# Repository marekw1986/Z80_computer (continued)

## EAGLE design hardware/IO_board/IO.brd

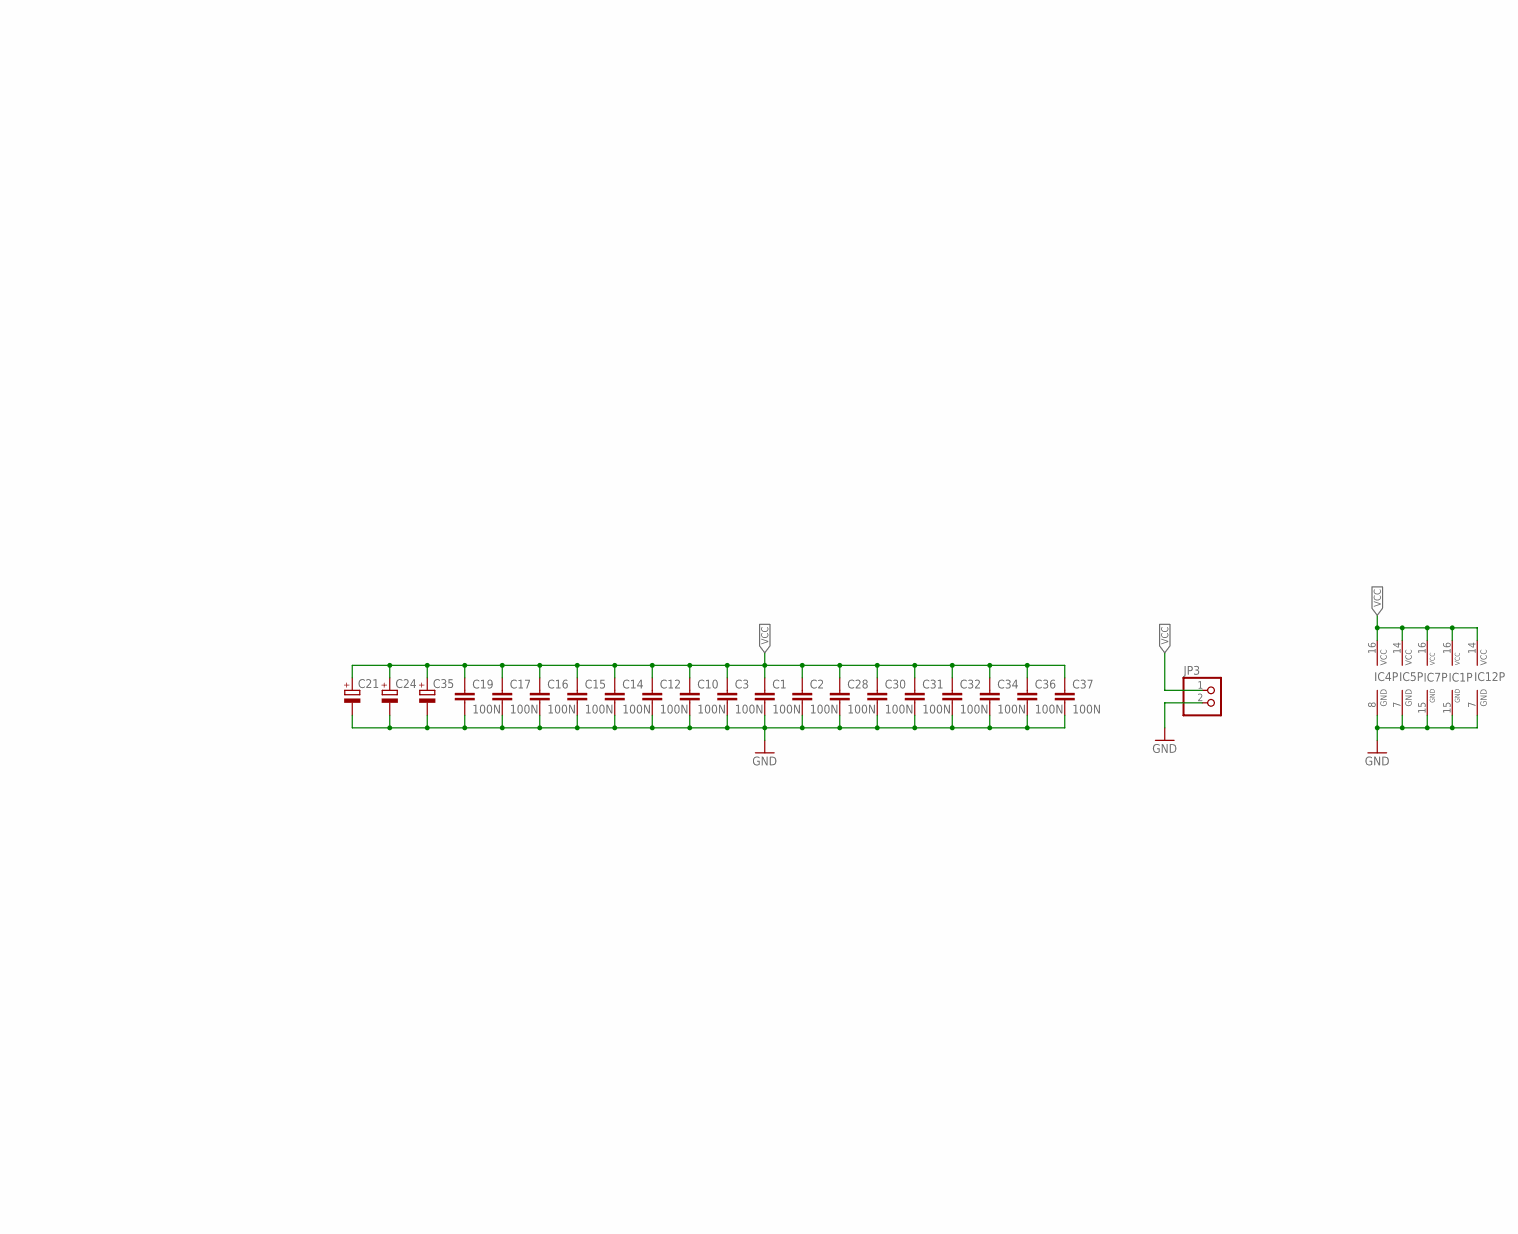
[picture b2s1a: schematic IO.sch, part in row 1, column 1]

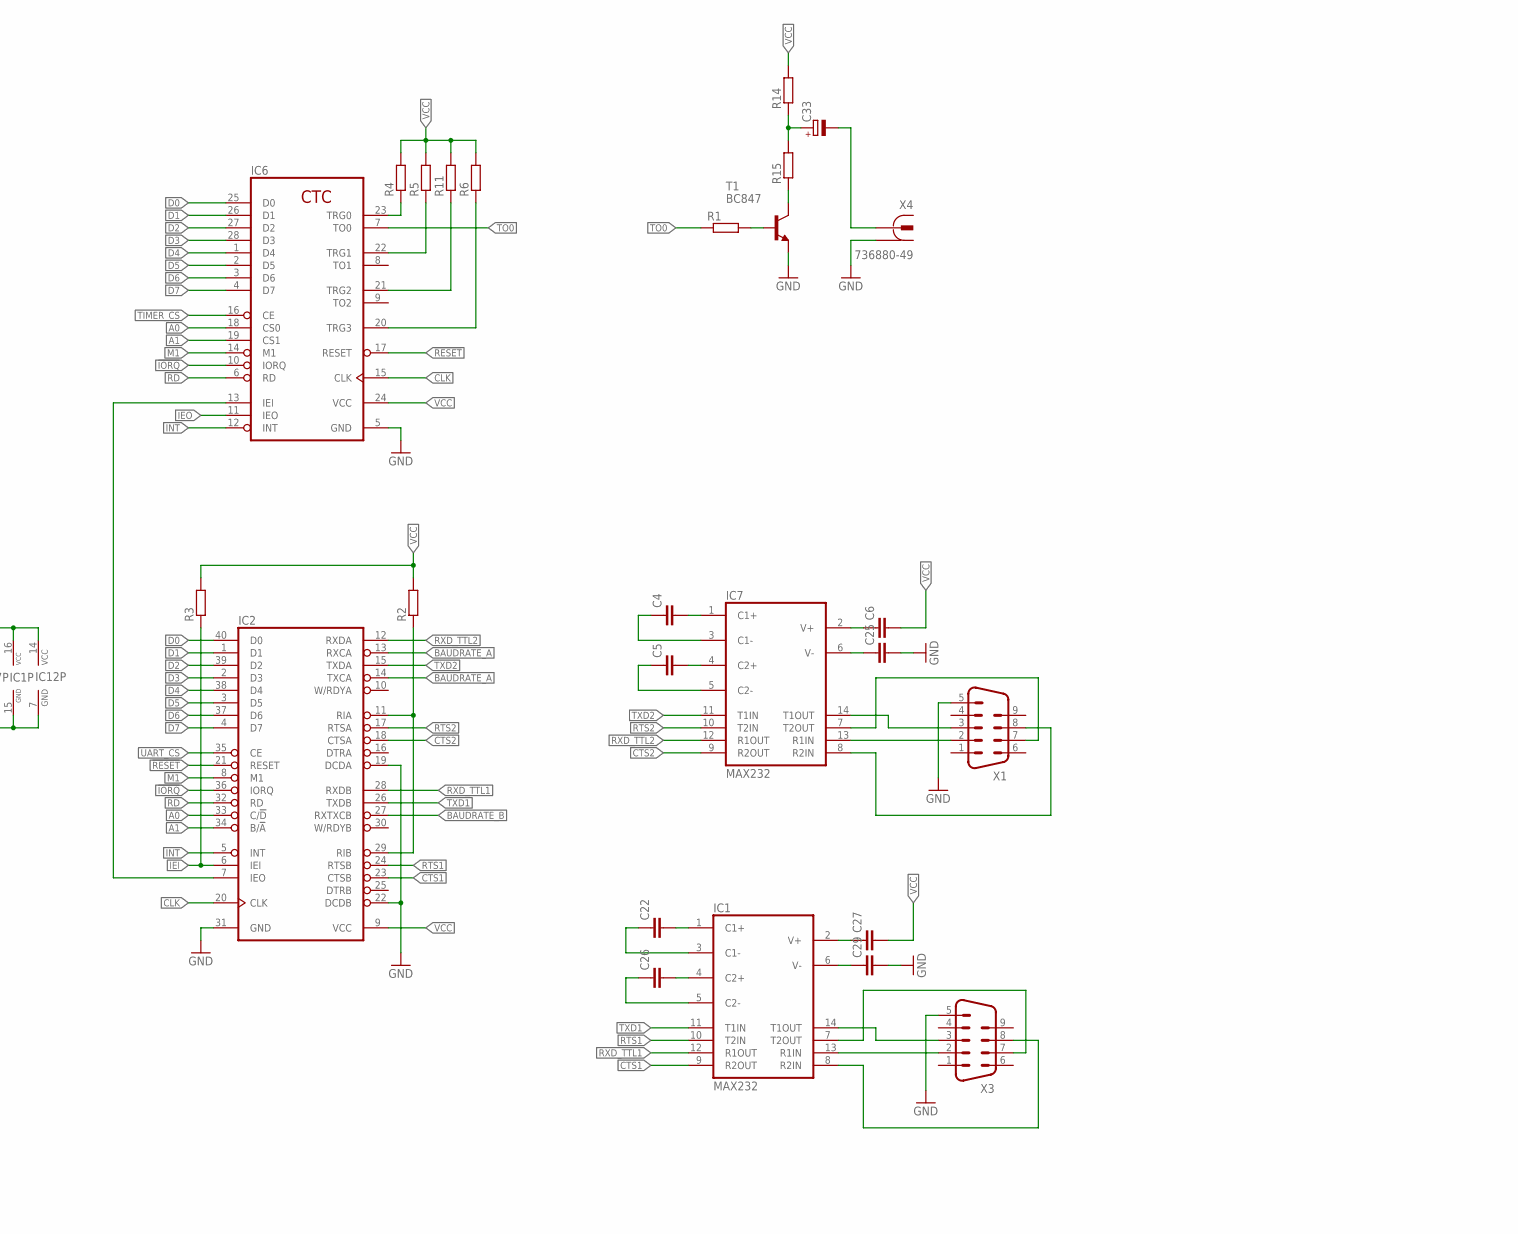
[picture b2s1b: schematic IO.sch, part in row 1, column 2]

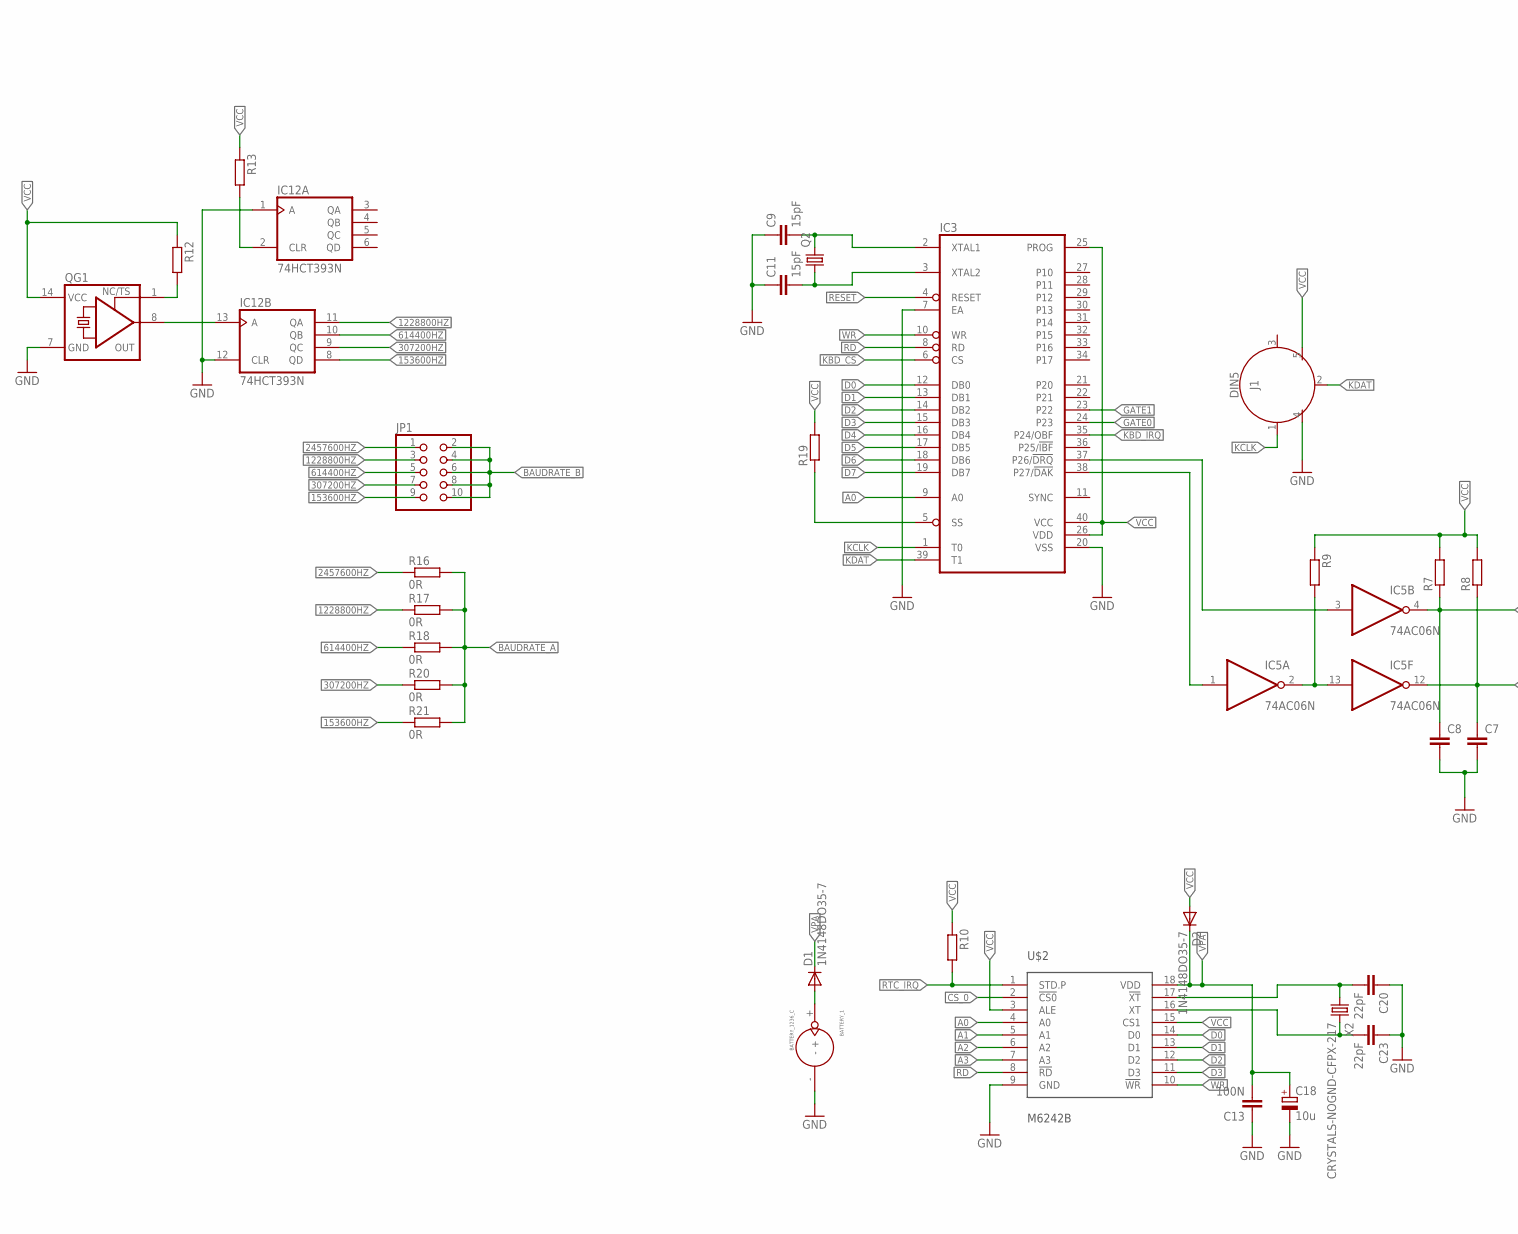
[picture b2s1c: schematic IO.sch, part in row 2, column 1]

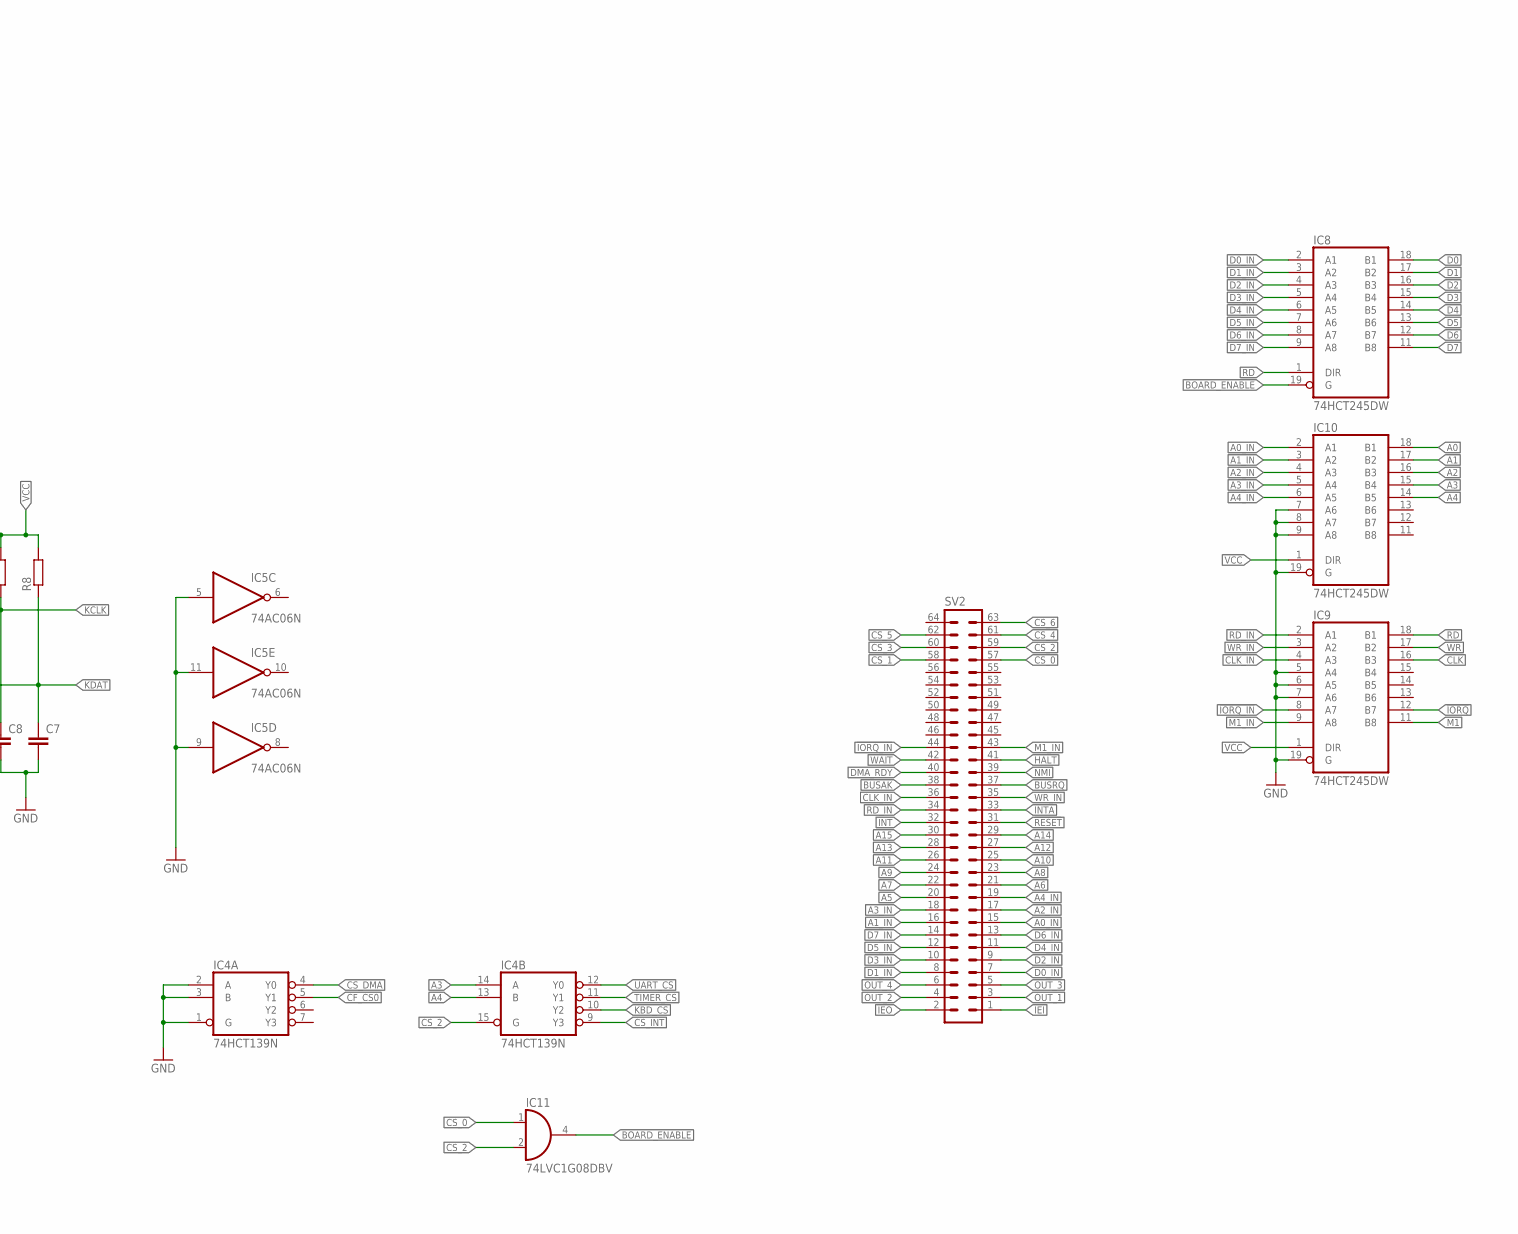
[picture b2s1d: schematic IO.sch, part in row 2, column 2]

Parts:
BATTERY_1: BATTERY_1236_C
C1, C3, C10, C12, C13, C14, C15, C16, C17, C19, C28, C30, C31, C32, C34, C36, C37: 100N; C0603
C2: 100N; C1206
C4, C5, C6, C7, C8, C22, C25, C26, C27, C29: C-EUC0603; C0603
C9, C11: 15pF; C0603
C18: 10u; SMC_B
C20, C23: 22pF; C0603
C21, C24: CPOL-EUSMCB; SMC_B
C33: CPOL-EUE2-4; E2-4
C35: CPOL-EUE5-10.5; E5-10,5
D1, D2: 1N4148DO35-7; DO35-7
IC1, IC7: MAX232; DIL16
IC2: Z80DART; DIL40
IC3: UPI-8042AH; DIL40
IC4: 74HCT139N; DIL16
IC5: 74AC06N; DIL14
IC6: Z80CTC; DIL28
IC8, IC9, IC10: 74HCT245DW; SO20W
IC11: 74LVC1G08DBV; SOT23-5
IC12: 74HCT393N; DIL14
J1: DIN5; DIN5-RA-PTH
JP1: PINHD-2X5; 2X05
JP3: PINHD-1X2/90; 1X02/90
Q2: CRYSTALHC49S; HC49/S
QG1: XO-14; DIL14S
R1, R2, R4, R5, R9, R10, R11, R12, R13, R15: R-EU_R0603; R0603
R3, R6, R19: R-EU_0204/5; 0204/5
R7, R14: R-EU_0204/7; 0204/7
R8: R-EU_M0805; M0805
R16, R17, R18, R20, R21: 0R; R0603
SV2: ML64L
T1: BC847; SOT23
U$2: M6242B; DIL18
X1, X3: M09HP
X2: CRYSTALS-NOGND-CFPX-217; 3.2X1.5-2-PAD
X4: 736880-49

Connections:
153600HZ: IC12.8 (QD), JP1.9, R21.1
307200HZ: IC12.9 (QC), JP1.7, R20.1
614400HZ: IC12.10 (QB), JP1.5, R18.1
1228800HZ: IC12.11 (QA), JP1.3, R17.1
2457600HZ: IC12.13 (A), JP1.1, QG1.8 (OUT), R16.1
!IORQ: IC2.36 (IORQ), IC6.10 (IORQ), IC9.12 (B7)
!IORQ_IN: IC9.8 (A7), SV2.44
!RESET: IC2.21 (RESET), IC3.4 (RESET), IC6.17 (RESET), SV2.31
A0: IC2.33 (C/!D), IC3.9 (A0), IC6.18 (CS0), IC10.18 (B1), U$2.4 (A0)
A0_IN: IC10.2 (A1), SV2.15
A1: IC2.34 (B/!A), IC6.19 (CS1), IC10.17 (B2), U$2.5 (A1)
A1_IN: IC10.3 (A2), SV2.16
A2: IC10.16 (B3), U$2.6 (A2)
A2_IN: IC10.4 (A3), SV2.17
A3: IC4.14 (A), IC10.15 (B4), U$2.7 (A3)
A3_IN: IC10.5 (A4), SV2.18
A4: IC4.13 (B), IC10.14 (B5)
A4_IN: IC10.6 (A5), SV2.19
A5: SV2.20
A6: SV2.21
A7: SV2.22
A8: SV2.23
A9: SV2.24
A10: SV2.25
A11: SV2.26
A12: SV2.27
A13: SV2.28
A14: SV2.29
A15: SV2.30
BAUDRATE_A: IC2.13 (RXCA), IC2.14 (TXCA), R16.2, R17.2, R18.2, R20.2, R21.2
BAUDRATE_B: IC2.27 (RXTXCB), JP1.2, JP1.4, JP1.6, JP1.8, JP1.10
BOARD_ENABLE: IC8.19 (G), IC11.4 (O)
BUSAK: SV2.38
BUSRQ: SV2.37
CF_CS0: IC4.5 (Y1)
CLK: IC2.20 (CLK), IC6.15 (CLK), IC9.16 (B3)
CLK_IN: IC9.4 (A3), SV2.36
CS_0: IC11.1 (I0), SV2.57, U$2.2 (!CS0)
CS_1: SV2.58
CS_2: IC4.15 (G), IC11.2 (I1), SV2.59
CS_3: SV2.60
CS_4: SV2.61
CS_5: SV2.62
CS_6: SV2.63
CS_DMA: IC4.4 (Y0)
CS_INT: IC4.9 (Y3)
CTS1: IC1.9 (R2OUT), IC2.23 (CTSB)
CTS1_IN: IC1.8 (R2IN), X3.8
CTS2: IC2.18 (CTSA), IC7.9 (R2OUT)
D0: IC2.40 (D0), IC3.12 (DB0), IC6.25 (D0), IC8.18 (B1), U$2.14 (D0)
D0_IN: IC8.2 (A1), SV2.7
D1: IC2.1 (D1), IC3.13 (DB1), IC6.26 (D1), IC8.17 (B2), U$2.13 (D1)
D1_IN: IC8.3 (A2), SV2.8
D2: IC2.39 (D2), IC3.14 (DB2), IC6.27 (D2), IC8.16 (B3), U$2.12 (D2)
D2_IN: IC8.4 (A3), SV2.9
D3: IC2.2 (D3), IC3.15 (DB3), IC6.28 (D3), IC8.15 (B4), U$2.11 (D3)
D3_IN: IC8.5 (A4), SV2.10
D4: IC2.38 (D4), IC3.16 (DB4), IC6.1 (D4), IC8.14 (B5)
D4_IN: IC8.6 (A5), SV2.11
D5: IC2.3 (D5), IC3.17 (DB5), IC6.2 (D5), IC8.13 (B6)
D5_IN: IC8.7 (A6), SV2.12
D6: IC2.37 (D6), IC3.18 (DB6), IC6.3 (D6), IC8.12 (B7)
D6_IN: IC8.8 (A7), SV2.13
D7: IC2.4 (D7), IC3.19 (DB7), IC6.4 (D7), IC8.11 (B8)
D7_IN: IC8.9 (A8), SV2.14
DMA_RDY: SV2.40
GATE0: IC3.24 (P23)
GATE1: IC3.23 (P22)
GND: BATTERY_1.-, C1.2, C2.2, C3.2, C7.2, C8.2, C9.1, C10.2, C11.1, C12.2, C13.1, C14.2, C15.2, C16.2, C17.2, C18.-, C19.2, C20.1, C21.-, C23.1, C24.-, C25.2, C28.2, C29.2, C30.2, C31.2, C32.2, C34.2, C35.-, C36.2, C37.2, IC1.15 (GND), IC2.19 (DCDA), IC2.22 (DCDB), IC2.31 (GND), IC3.7 (EA), IC3.20 (VSS), IC4.1 (G), IC4.2 (A), IC4.3 (B), IC4.8 (GND), IC5.5 (I), IC5.7 (GND), IC5.9 (I), IC5.11 (I), IC6.5 (GND), IC7.15 (GND), IC8.10 (GND), IC9.5 (A4), IC9.6 (A5), IC9.7 (A6), IC9.10 (GND), IC9.19 (G), IC10.7 (A6), IC10.8 (A7), IC10.9 (A8), IC10.10 (GND), IC10.19 (G), IC11.3 (GND), IC12.1 (A), IC12.7 (GND), IC12.12 (CLR), J1.4, JP3.2, QG1.7 (GND), T1.2 (E), U$2.9 (GND), X1.5, X3.5, X4.1, X4.1@1 (1), X4.1@2 (1)
HALT: SV2.41
IEI: IC2.6 (IEI), R3.1, SV2.1
IEO: IC6.11 (IEO), SV2.2
INT: IC2.5 (INT), IC6.12 (INT), SV2.32
INTA: SV2.33
KBD_CS: IC3.6 (CS), IC4.10 (Y2)
KBD_IRQ: IC3.35 (P24/OBF)
KCLK: C8.1, IC3.1 (T0), IC5.4 (O), J1.1, R7.1
KDAT: C7.1, IC3.39 (T1), IC5.12 (O), J1.2, R8.1
M1: IC2.8 (M1), IC6.14 (M1), IC9.11 (B8)
M1_IN: IC9.9 (A8), SV2.43
unnamed: IC1.7 (T2OUT), X3.7
unnamed: C22.2, IC1.1 (C1+)
unnamed: IC3.38 (P27/!DAK), IC5.1 (I)
unnamed: C26.2, IC1.4 (C2+)
unnamed: C26.1, IC1.5 (C2-)
unnamed: C22.1, IC1.3 (C1-)
unnamed: IC7.7 (T2OUT), X1.7
unnamed: IC7.13 (R1IN), X1.2
unnamed: C4.2, IC7.1 (C1+)
unnamed: C5.2, IC7.4 (C2+)
unnamed: C5.1, IC7.5 (C2-)
unnamed: C4.1, IC7.3 (C1-)
unnamed: C6.1, IC7.2 (V+)
unnamed: C25.1, IC7.6 (V-)
unnamed: C9.2, IC3.2 (XTAL1), Q2.2
unnamed: C11.2, IC3.3 (XTAL2), Q2.1
unnamed: IC3.37 (P26/!DRQ), IC5.3 (I)
unnamed: IC7.14 (T1OUT), X1.3
unnamed: C27.1, IC1.2 (V+)
unnamed: IC5.2 (O), IC5.13 (I), R9.2
unnamed: IC1.13 (R1IN), X3.2
unnamed: BATTERY_1.+, D1.A
unnamed: R1.2, T1.1 (B)
unnamed: R15.1, T1.3 (C)
unnamed: IC7.8 (R2IN), X1.8
unnamed: C29.1, IC1.6 (V-)
unnamed: C33.-, X4.2
unnamed: IC6.22 (TRG1), R5.1
unnamed: IC2.7 (IEO), IC6.13 (IEI)
unnamed: IC6.23 (TRG0), R4.1
unnamed: QG1.1 (TS), R12.2
unnamed: IC3.5 (SS), R19.1
unnamed: IC2.11 (RIA), IC2.29 (RIB), R2.1
unnamed: IC6.20 (TRG3), R6.1
unnamed: IC6.21 (TRG2), R11.1
unnamed: C33.+, R14.1, R15.2
unnamed: IC12.2 (CLR), R13.2
NMI: SV2.39
OUT_1: SV2.3
OUT_2: SV2.4
OUT_3: SV2.5
OUT_4: SV2.6
RD: IC2.32 (RD), IC3.8 (RD), IC6.6 (RD), IC8.1 (DIR), IC9.18 (B1), U$2.8 (!RD)
RD_IN: IC9.2 (A1), SV2.34
RTC_IRQ: R10.2, U$2.1 (STD.P)
RTS1: IC1.10 (T2IN), IC2.24 (RTSB)
RTS2: IC2.17 (RTSA), IC7.10 (T2IN)
RXD_TTL1: IC1.12 (R1OUT), IC2.28 (RXDB)
RXD_TTL2: IC2.12 (RXDA), IC7.12 (R1OUT)
SOSCI: C20.2, U$2.17 (!XT), X2.1
SOSCO: C23.2, U$2.16 (XT), X2.2
TIMER_CS: IC4.11 (Y1), IC6.16 (CE)
TO0: IC6.7 (TO0), R1.1
TXD1: IC1.11 (T1IN), IC2.26 (TXDB)
TXD1_OUT: IC1.14 (T1OUT), X3.3
TXD2: IC2.15 (TXDA), IC7.11 (T1IN)
UART_CS: IC2.35 (CE), IC4.12 (Y0)
VCC: C1.1, C2.1, C3.1, C6.2, C10.1, C12.1, C14.1, C15.1, C16.1, C17.1, C19.1, C21.+, C24.+, C27.2, C28.1, C30.1, C31.1, C32.1, C34.1, C35.+, C36.1, C37.1, D2.A, IC1.16 (VCC), IC2.9 (VCC), IC3.25 (PROG), IC3.26 (VDD), IC3.40 (VCC), IC4.16 (VCC), IC5.14 (VCC), IC6.24 (VCC), IC7.16 (VCC), IC8.20 (VCC), IC9.1 (DIR), IC9.20 (VCC), IC10.1 (DIR), IC10.20 (VCC), IC11.5 (VCC), IC12.14 (VCC), J1.5, JP3.1, QG1.14 (VCC), R2.2, R3.2, R4.2, R5.2, R6.2, R7.2, R8.2, R9.1, R10.1, R11.2, R12.1, R13.1, R14.2, R19.2, U$2.3 (ALE), U$2.15 (CS1)
VPA: C13.2, C18.+, D1.C, D2.C, U$2.18 (VDD)
WAIT: SV2.42
WR: IC3.10 (WR), IC9.17 (B2), U$2.10 (!WR)
WR_IN: IC9.3 (A2), SV2.35

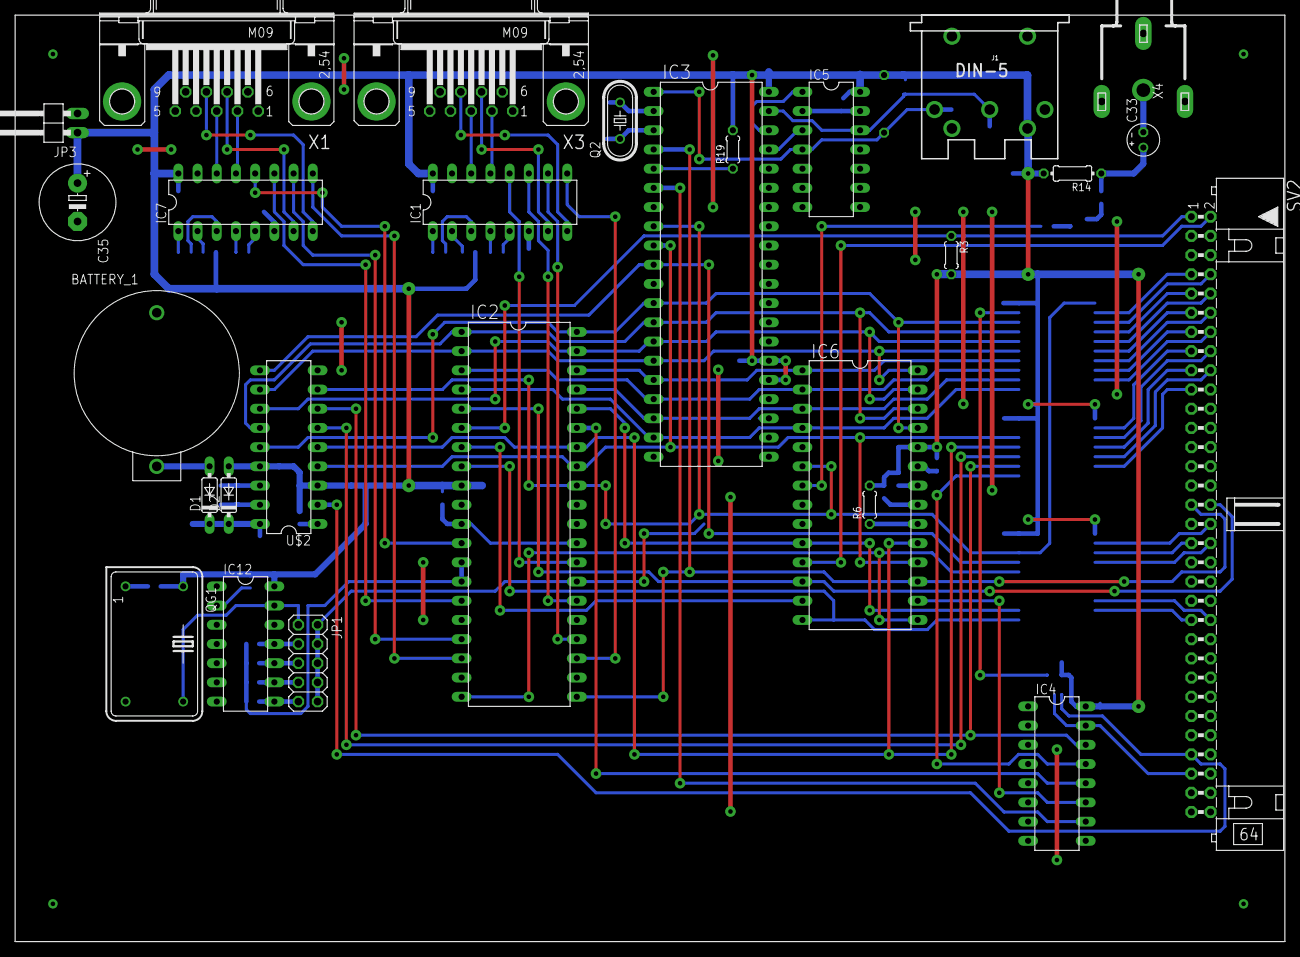
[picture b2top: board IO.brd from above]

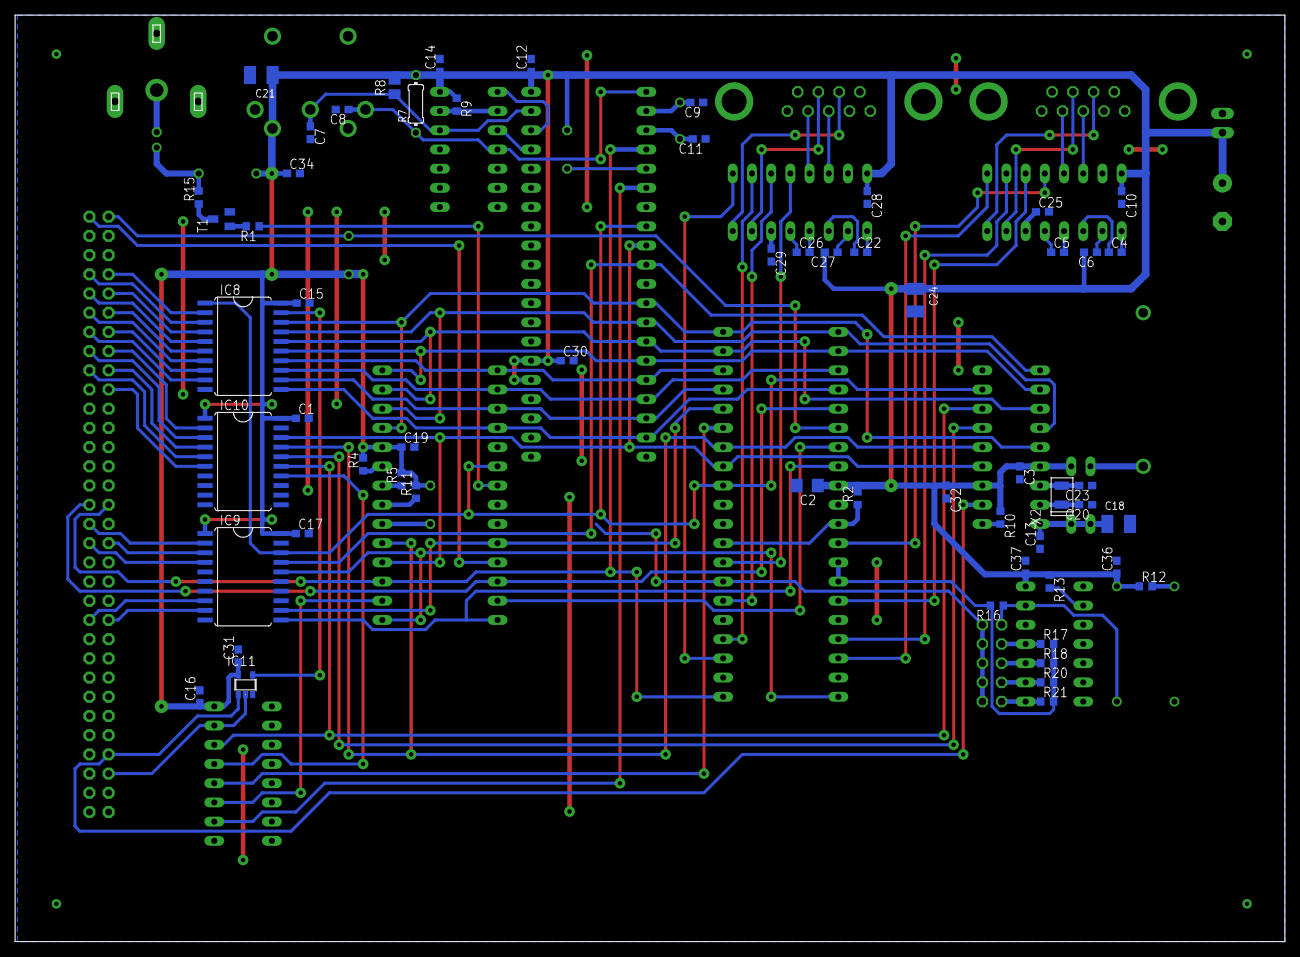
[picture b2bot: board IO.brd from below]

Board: 2 copper layers, 167.9 x 122.5 mm, 85 parts (58 on the bottom side), 109 nets.

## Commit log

2025-02-16 README.md added
2025-02-17 CPU board update
2025-02-23 bugs in CPU board design fixed
2025-02-23 GAL added
2025-02-23 code added
2025-02-25 I/O board added (work in progress)
2025-02-26 CPU board and I/O board update
2025-02-27 I/O board updated (work in progress)
2025-02-27 IO board update (work in progress)
2025-02-27 IO board update
2025-02-28 CPU and I/O board update
2025-03-01 Audio circuit added to I/O board
2025-03-01 Capacitors added to I/O board
2025-03-06 Experiments with Z80 DART
2025-03-06 Minor bug fixed
2025-03-06 TinyBasic and CP/M bootloader added (work in progress)
2025-03-08 Separate baudrate generator on I/O board
2025-03-09 I/O board: 0R resistors added to set baudrate at DART channel A
2025-03-11 CP/M BIOS added
2025-03-12 UART reconfigured after adding hardware baudrate generator
2025-03-13 Calculating of sector in BLKDAT optimized for size with loop
2025-03-13 Local version of drivers and libraries used by BIOS created to save space. BIOS now uses own set of local variables. Dependency from bootloader removed. Memory rearanged.
2025-03-13 BIOS prepared for read optimization/caching
2025-03-13 Minor changes
2025-03-13 Experiments with writing (work in progress)
2025-03-13 Writing works but needs to be improved
2025-03-14 Fix in CF card driver for CP/M BIOS
2025-03-14 Cached reads work. Reading addresses of partitions added. Adding partition address at read and write (WORK IN PROGRESS)
2025-03-14 Chacing optimized (read after successful write scenario)
2025-03-14 Minor fix
2025-03-14 Write optimized (first sector of new track)
2025-03-14 Only four partition can be accessed
2025-03-14 Calculating CFLBA from partition table
2025-03-14 Disk number is used to calculate partition addr
2025-03-15 Checking if calculated LBA is proper
2025-03-15 Checking if MBR was loaded properly before initializing partition table
2025-03-16 Checking if CP/M bootloader finished load successfully
2025-03-17 Minor refactoring
2025-04-16 Writes to 74273 on rising edge and synchronized with system clock
2025-04-28 Bug in CPU board fixed
2025-04-29 Standalone bootloader added
2025-04-29 TinyBasic removed from ROM
2025-04-29 Dependencies from bootloader removed from CP/M bios code
2025-09-05 Z80 version of bootloader code generated
2025-09-05 Revert "Z80 version of bootloader code generated"
    This reverts commit 0d694d46e492795432687681be2e0b371d8f6f75.
2025-09-08 Bootloader rewritten in Z80 assembly
2025-09-09 Porting bootloader to Z80 assembly (work in progress)
2025-09-09 Porting CP/M BIOS to Z80 assebly (work in progress)
2025-09-09 Differences between 8080 and Z80 code fixed
2025-09-10 Optimizing by using Z80 instructions instead of 8080
2025-09-10 Optimizing BIOS with Z80 instructions
2025-09-10 Porting CP/M BIOS to Z80 assembly
2025-09-11 Makefile updated
2025-09-11 Bug in Makefile fixed
2025-09-11 MVI A, 00H replaced with XOR A to preserve memory and CPU cycles
2025-09-11 LD A, 00H replaced with XOR A to preserve memory and CPU cycles
2025-09-11 CPI 00H replaced with OR A
2025-09-11 CP 00H replaced with OR A
2025-09-11 Revert "CPI 00H replaced with OR A"
    This reverts commit bcb5063a4d61262c1f144f445e602dbecd47e46a.
2025-09-11 Revert "MVI A, 00H replaced with XOR A to preserve memory and CPU cycles"
    This reverts commit b277eeb6439997e5d81042ee541484a515472bea.
2025-09-11 MVI A, 00H replaced with XRA A
2025-09-11 CPI 00H replaced with ORA A
2025-09-13 CP/M bios rewritten in Z80 assembly. Now it generates binary identical to 8080 version. Baseline for firther optimizations
2025-09-13 SP initialized dirrectly, without using HL register
2025-09-13 Slight optimizations at WBOOT. Commented code and unused debug routines removed.
2025-09-13 Further optimizations, unused code removal
2025-09-13 Minor optimizations in READ routine
2025-09-13 Using LDIR instruction in READ instead of MEMCOPY
2025-09-13 Use LDIR for writes instead of MEMCOPY
2025-09-13 Using LDIR for filling memory
2025-09-13 Unused MEMCOPY routine removed, CRC16 routine updated to Z80 optimized version
2025-09-14 Bug in READ procedure fixed
2025-09-14 Bug fix in 8080 version
2025-09-14 MVI A, 0 replaced with XRA A
2025-09-14 LD A, 0 replaced with XOR A
2025-09-14 Instructions encoded with opcodes replaced with proper mnemonics
2025-09-14 Default target in bootloader makefile changed to bootloader.bin. Old bootloader.hex made with a85 removed.
2025-09-14 CRC16 in common/utils_z80.asm replaced with Z80 optimizedversion
2025-09-16 Minor optimizations in Z80 utils and cf driver
2025-09-16 Minor optimization in Z80 version of hexdump
2025-09-16 Unused 8080 code removed
2025-09-22 Makefile added
2025-09-22 Deffered writes backported from Z180 project
2025-09-22 Termorary workaround for deferred write issue
2025-09-23 Unused strings removed. CF related strings moved to cf.asm
2026-06-21 Deffered write fix
